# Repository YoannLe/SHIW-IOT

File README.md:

# SmartHome-In-Wall-IOT

Smart Home in-wall IOT modules with ESP8266 designed to be used with Arduino and REST API or Souliss, OpenHab,...

Goals and prospects:
* Modules must fit in standard electric wall boxes (European standard wallbox ⌀67x40mm)
* Limit the number of components for DIY feasibility
* Common logic board and different power boards

This GitHub contains PCB files and source code samples.

##Hardware
Schematic and PCB:
* Logic Board:
 * Made for ESP-07 or EPS-12 ESP8266 module
 * Drives all power boards
 * Include relay driver, I2C port for Temperatur and Humidity sensor
* Power Boards:
 * Relays version: Relays Board, 2 dual coils relays, for curtains, garage doors...
 * FilPilote version: Generate signals for drive Electric Heaters by Fil Pilote
 * Dimmer version: Triac with zero crossing circuit to dim incandescent lamps

##Software
Arduino source code sample for each module, can works out of the box but understanding Souliss architecture and configration is required to build a Smart Home Network with a lot of nodes.

##Documentation

##References
[Arduino and ESP8266 GitHub](https://github.com/esp8266/Arduino)

[Souliss Wiki](https://github.com/souliss/souliss/wiki) 

[Souliss Website](http://souliss.net/)

[Fil Pilote] (http://www.radiateur-electrique.org/fil-pilote-radiateur.php)

# License

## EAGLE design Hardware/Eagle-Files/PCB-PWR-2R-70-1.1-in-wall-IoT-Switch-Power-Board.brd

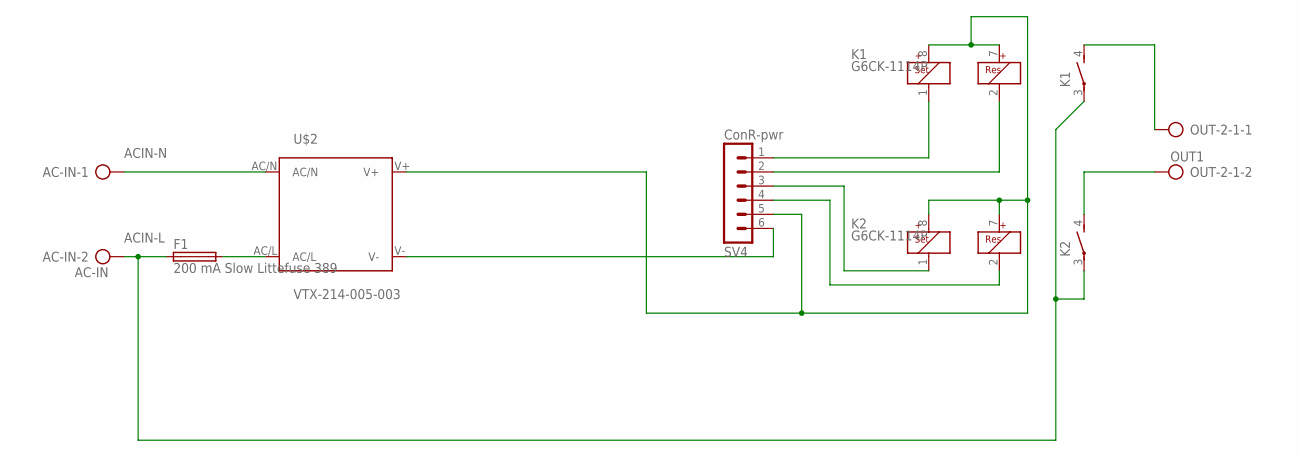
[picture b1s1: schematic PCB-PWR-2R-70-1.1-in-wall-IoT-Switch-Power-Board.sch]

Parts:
AC-IN: AC-IN; AK500/2-H
F1: 200 mA Slow Littefuse 389; TE5
K1, K2: G6CK-1114P; G6CK-1117P
OUT-2-1: OUT1; AK500/2-H
SV4: ConR-pwr; MA06-1
U$2: VTX-214-005-003

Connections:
ACIN-L: AC-IN.2, F1.1, K1.3, K2.3
ACIN-N: AC-IN.1, U$2.AC/N
unnamed: K1.4 (S), OUT-2-1.1
unnamed: K2.4 (S), OUT-2-1.2
unnamed: SV4.6, U$2.V-
unnamed: F1.2, U$2.AC/L
unnamed: K1.7 (R+), K1.8 (S+), K2.7 (R+), K2.8 (S+), SV4.5, U$2.V+
unnamed: K1.1 (S-), SV4.1
unnamed: K1.2 (R-), SV4.2
unnamed: K2.1 (S-), SV4.3
unnamed: K2.2 (R-), SV4.4

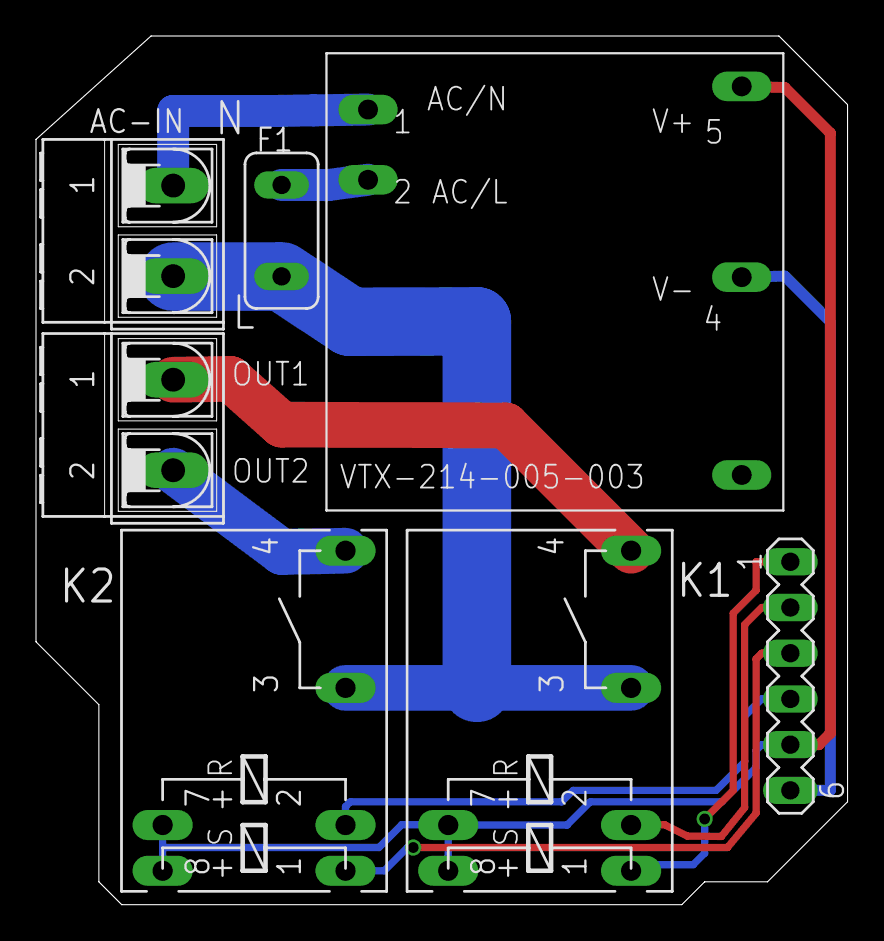
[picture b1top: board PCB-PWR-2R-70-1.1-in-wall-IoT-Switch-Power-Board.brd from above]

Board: 2 copper layers, 45.1 x 48.3 mm, 7 parts (0 on the bottom side), 11 nets.

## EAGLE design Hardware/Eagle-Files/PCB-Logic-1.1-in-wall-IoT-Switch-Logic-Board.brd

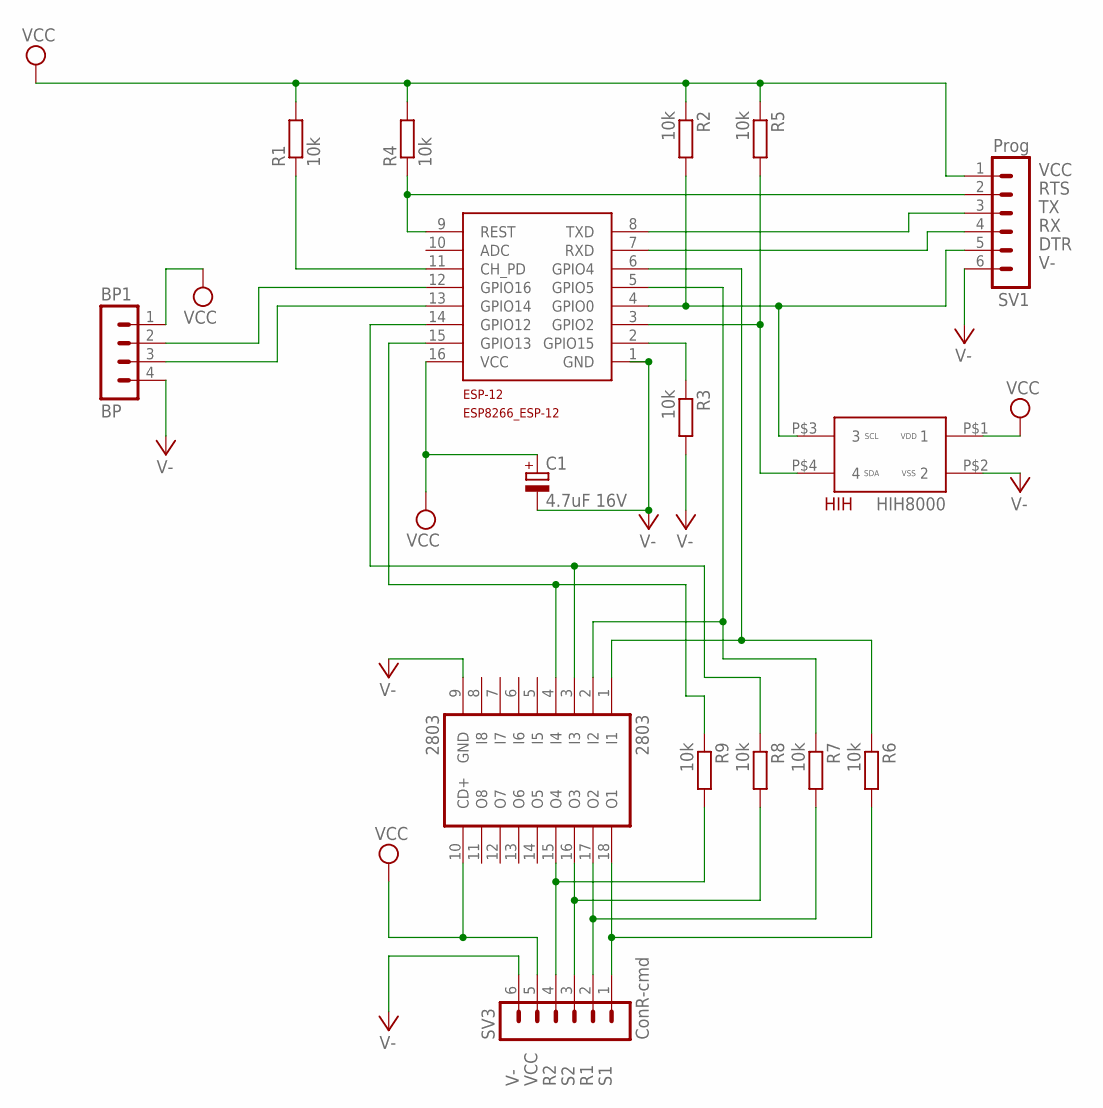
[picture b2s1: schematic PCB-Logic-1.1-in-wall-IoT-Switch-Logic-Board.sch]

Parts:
2803: 2803; SO18W
BP: BP1; MA04-1
C1: 4.7uF 16V; A/3216-18W
ESP-12: ESP8266_ESP-12; ESP8266-ESP12
HIH: HIH8120-021-001; SIP4
R1, R2, R3, R4, R5, R6, R7, R8, R9: 10k; R1206W
SV1: Prog; MA06-1
SV3: ConR-cmd; MA06-1

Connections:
BPDW: BP.3, ESP-12.13 (GPIO14)
BPUP: BP.2, ESP-12.12 (GPIO16)
DTR: ESP-12.4 (GPIO0), HIH.P$3 (3), R2.2, SV1.5
unnamed: ESP-12.3 (GPIO2), HIH.P$4 (4), R5.2
unnamed: ESP-12.2 (GPIO15), R3.1
unnamed: 2803.3 (I3), ESP-12.14 (GPIO12), R8.1
unnamed: 2803.4 (I4), ESP-12.15 (GPIO13), R9.1
unnamed: 2803.2 (I2), ESP-12.5 (GPIO5), R7.1
unnamed: ESP-12.11 (CH_PD), R1.1
unnamed: 2803.1 (I1), ESP-12.6 (GPIO4), R6.1
R1: 2803.17 (O2), R7.2, SV3.2
R2: 2803.15 (O4), R9.2, SV3.4
RTS: ESP-12.9 (REST), R4.1, SV1.2
RX: ESP-12.7 (RXD), SV1.4
S1: 2803.18 (O1), R6.2, SV3.1
S2: 2803.16 (O3), R8.2, SV3.3
TX: ESP-12.8 (TXD), SV1.3
V-: 2803.9 (GND), BP.4, C1.-, ESP-12.1 (GND), HIH.P$2 (2), R3.2, SV1.6, SV3.6
VCC: 2803.10 (CD+), BP.1, C1.+, ESP-12.16 (VCC), HIH.P$1 (1), R1.2, R2.1, R4.2, R5.1, SV1.1, SV3.5

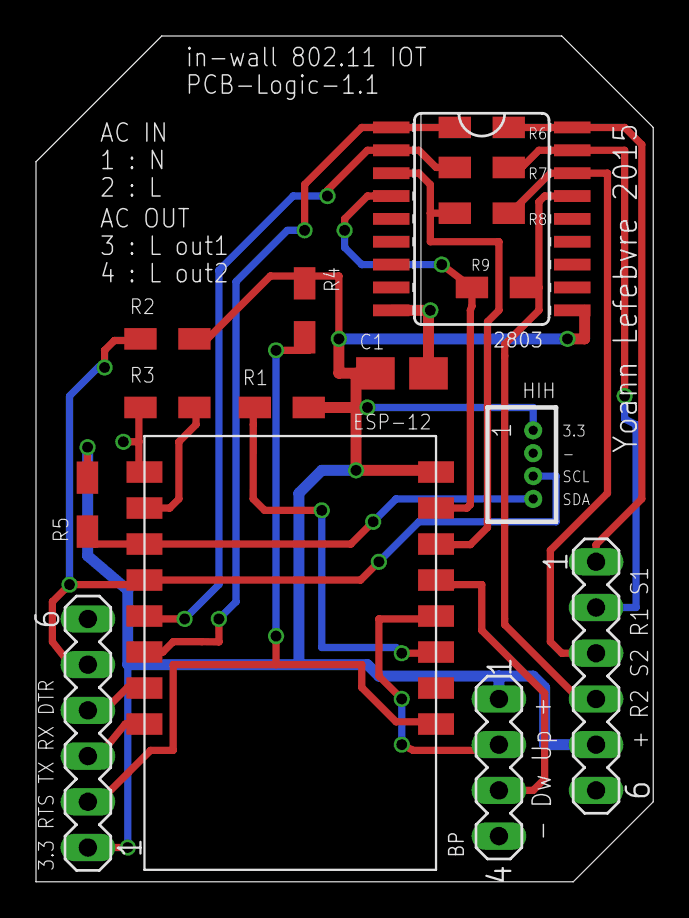
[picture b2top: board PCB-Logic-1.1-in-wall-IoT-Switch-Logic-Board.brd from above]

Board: 2 copper layers, 34.3 x 47.0 mm, 16 parts (0 on the bottom side), 19 nets.

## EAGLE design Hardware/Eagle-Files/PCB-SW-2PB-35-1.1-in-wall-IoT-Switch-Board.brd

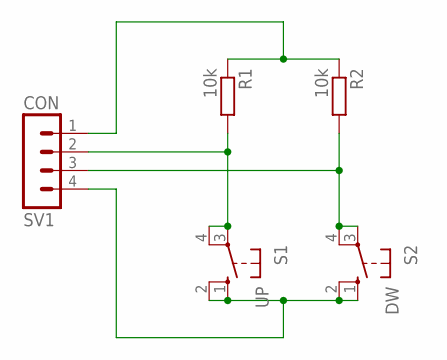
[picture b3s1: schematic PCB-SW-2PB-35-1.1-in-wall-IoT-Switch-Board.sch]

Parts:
R1, R2: 10k; R1206W
S1: UP; B3F-40XX
S2: DW; B3F-40XX
SV1: CON; MA04-1

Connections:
unnamed: R2.2, S2.3, S2.4 (P1), SV1.3
unnamed: R1.2, S1.3, S1.4 (P1), SV1.2
unnamed: R1.1, R2.1, SV1.1
unnamed: S1.1 (S), S1.2 (S1), S2.1 (S), S2.2 (S1), SV1.4

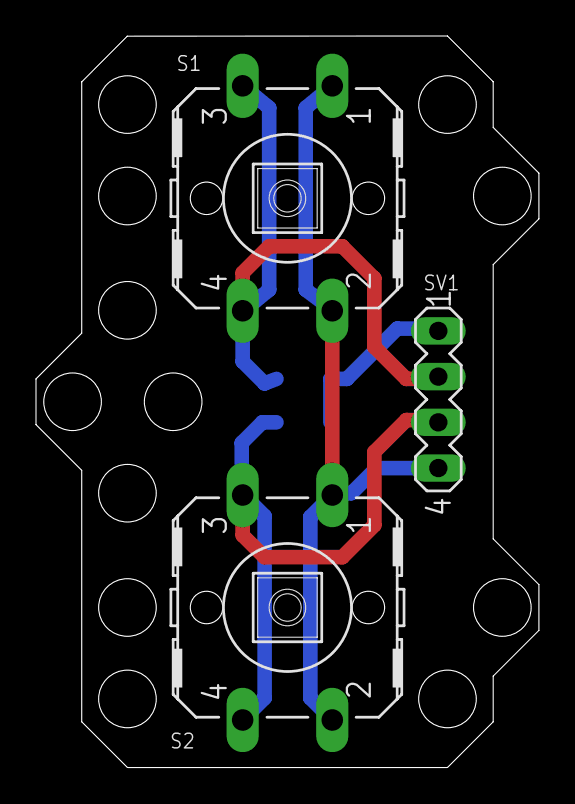
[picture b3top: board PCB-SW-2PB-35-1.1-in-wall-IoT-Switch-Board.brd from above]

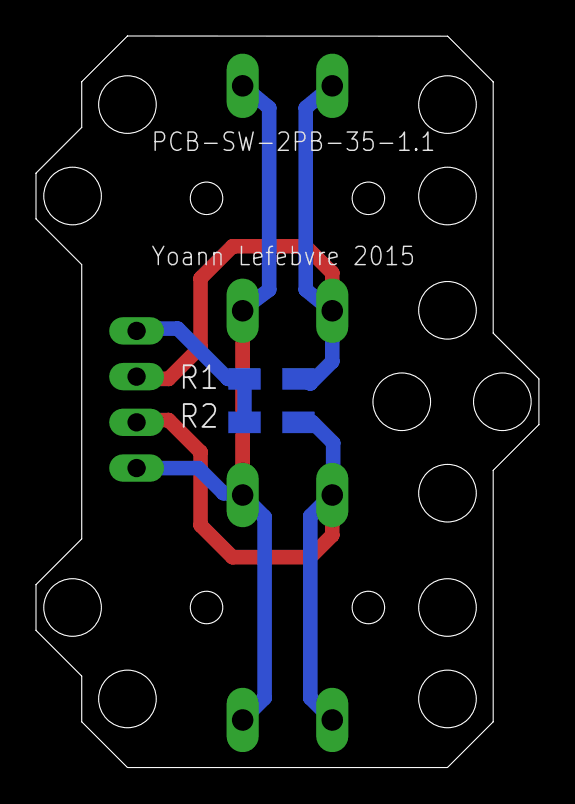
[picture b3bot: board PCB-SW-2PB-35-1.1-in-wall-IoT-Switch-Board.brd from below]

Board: 2 copper layers, 27.9 x 40.6 mm, 5 parts (2 on the bottom side), 4 nets.

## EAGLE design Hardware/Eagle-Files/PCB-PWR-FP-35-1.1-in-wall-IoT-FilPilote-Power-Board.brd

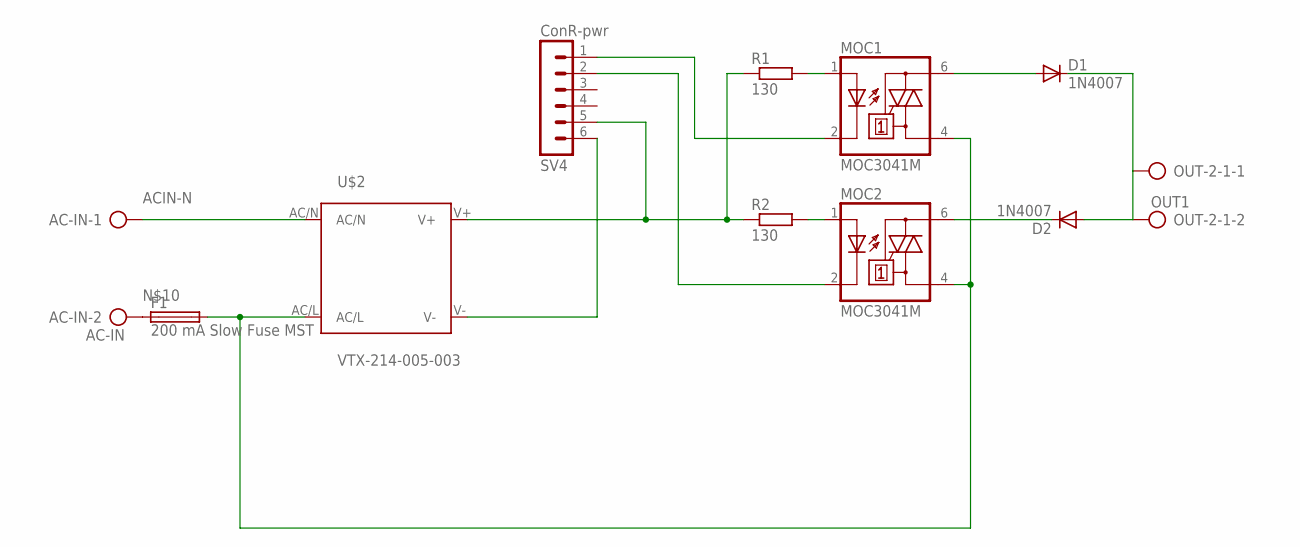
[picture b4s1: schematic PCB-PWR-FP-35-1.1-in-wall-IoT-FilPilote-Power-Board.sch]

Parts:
AC-IN: AC-IN; AK500/2-H
D1, D2: 1N4007; DO41-10
F1: 200 mA Slow Fuse MST; TE5
MOC1, MOC2: MOC3041M; DIL06
OUT-2-1: OUT1; AK500/2-H
R1, R2: 130; R1206W
SV4: ConR-pwr; MA06-1
U$2: VTX-214-005-003

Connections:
ACIN-L: F1.2, MOC1.4 (A1), MOC2.4 (A1), U$2.AC/L
ACIN-N: AC-IN.1, U$2.AC/N
unnamed: D1.C, D2.A, OUT-2-1.1, OUT-2-1.2
unnamed: D1.A, MOC1.6 (A2)
unnamed: SV4.6, U$2.V-
unnamed: D2.C, MOC2.6 (A2)
unnamed: MOC1.2 (C), SV4.1
unnamed: MOC2.2 (C), SV4.2
unnamed: MOC1.1 (A), R1.2
unnamed: MOC2.1 (A), R2.2
unnamed: AC-IN.2, F1.1
unnamed: R1.1, R2.1, SV4.5, U$2.V+

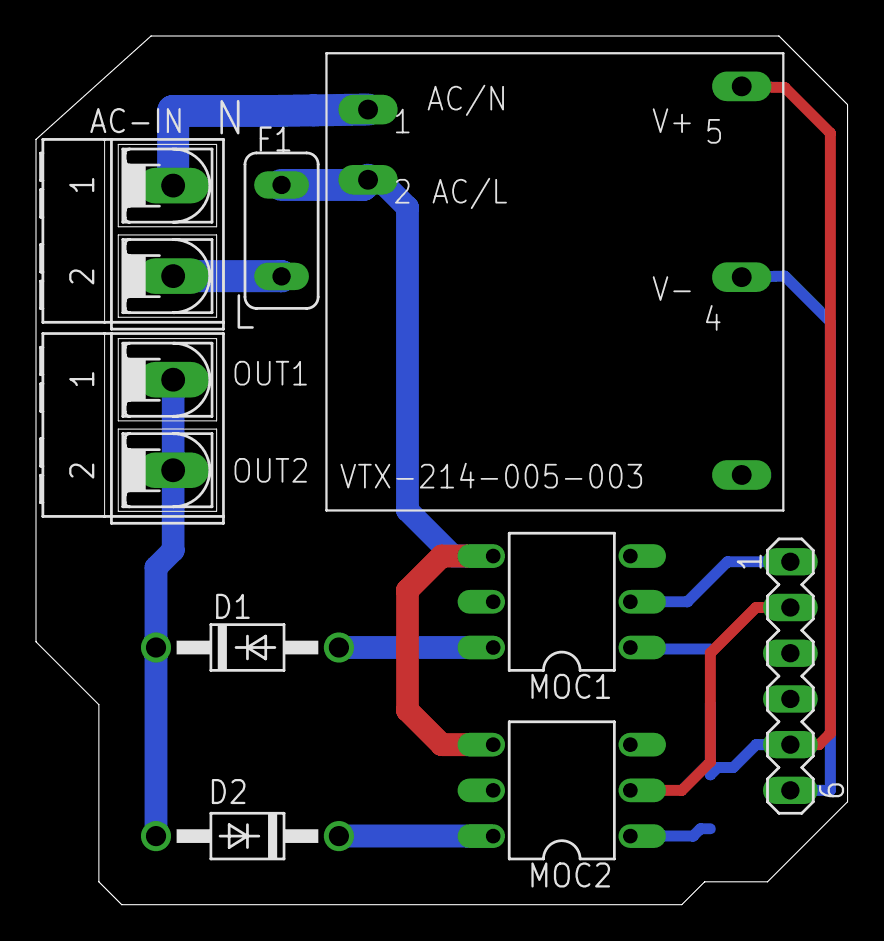
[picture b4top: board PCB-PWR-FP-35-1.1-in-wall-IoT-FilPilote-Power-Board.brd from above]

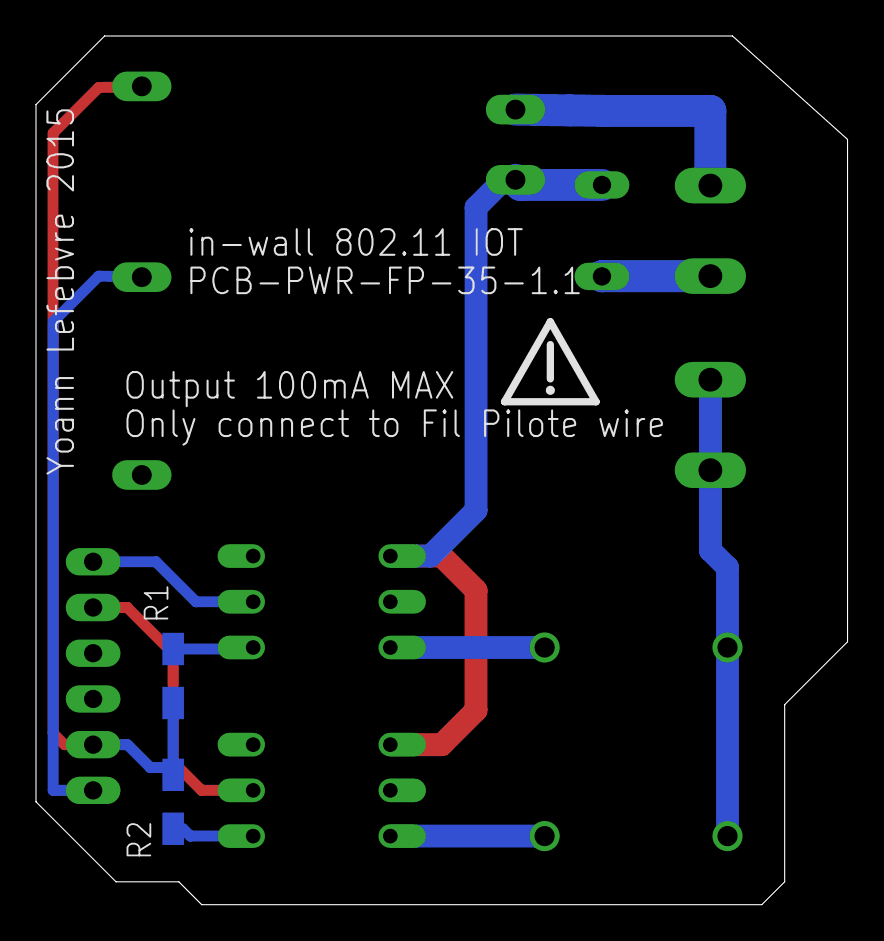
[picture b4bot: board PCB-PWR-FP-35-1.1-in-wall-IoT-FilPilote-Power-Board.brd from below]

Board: 2 copper layers, 45.1 x 48.3 mm, 11 parts (2 on the bottom side), 12 nets.

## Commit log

2015-11-11 Hardwares files
2015-11-11 Hardware clean files
2015-11-11 Arduino souliss sample file
